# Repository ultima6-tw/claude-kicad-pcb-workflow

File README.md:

# How we design a PCB with Claude Code and KiCad

> **Status: workflow demonstration, NOT a verified design.**
> The example board in this repo has never been fabricated or powered on.
> Its layout is unfinished: signal routing for one of four cells is done, but power and ground planes are still in progress.
> Do not send these files to a fab, and do not reuse the circuit without your own review.
>
> **High-voltage warning:** the example design floats on a +300 V platform and uses ±52 V rails.
> If you build anything similar, follow proper isolation, creepage and safety practices. The DRC rules here only check clearance, not creepage.

This repo documents the whole process we used to design a PCB with an AI assistant (Claude Code), from datasheets to Gerber files.

The example is a 16-channel high-voltage arbitrary waveform generator: four FPGA modules (Trenz TE0720), each driving four AD8460 DACs, with isolated power on one 300 × 290 mm, 6-layer board.

The main idea: **the AI handles the schematic the way it handles code.** Connections are written as text, repeated structure is generated by scripts, and every step is checked by a program. Then KiCad turns the result into a board.

## The process

```
 1. Setup            KiCad 10 + KiCad MCP server + Claude Code
 2. Datasheets       every connection traced to a datasheet section
 3. Parts            built-in → vendor (with fixes) → generated from datasheet
 4. Sub-circuits     parts + net labels on pins, no wires          → ERC
 5. Hierarchy        generated by script                           → pin-by-pin check
 6. Into the board   kicad-cli netlist written into pads           → schematic parity
 7. Design rules     net classes + high-voltage clearance          → negative test
 8. Placement        script (or KiCad GUI)
 9. Routing          script (or KiCad GUI)                         → DRC
10. Output           Gerber, drill, BOM, position files
```

### 1. Setup
KiCad 10.0.6, [mixelpixx/KiCAD-MCP-Server](https://github.com/mixelpixx/KiCAD-MCP-Server), and Claude Code on macOS. Install steps and common problems are in [`docs/kicad-mcp-setup.md`](docs/kicad-mcp-setup.md).

We first ran a tiny LED + resistor board through the full flow (schematic → ERC → PCB → DRC → Gerber) to make sure the tool chain works before starting real work.

### 2. Read the datasheets first
Before drawing anything, Claude reads the datasheets and application notes and writes down where each connection comes from (for example, "AD8460 datasheet, Figure 58"). If a choice has no reference, it is labelled **"no reference, design decision"**, so a reviewer knows what to double-check. These notes are kept next to the design as a running log.

### 3. Parts
In this order:
1. **KiCad built-in libraries** where possible.
2. **Vendor libraries** (Ultra Librarian), imported by a script that also fixes their errors. We found wrong pin types, an exposed pad with no matching symbol pin, and one part with the wrong package.
3. **Generated from the datasheet** when nothing exists. For example, `gen_te0720.py` reads connector pins from the module's schematic PDF. Every dimension is then compared with the official drawing.

### 4. Sub-circuits
Each sub-circuit (one DAC channel, the power stage) is drawn through the MCP server. Parts are placed, and **net labels are put directly on pins instead of drawing wires**. The schematic is then effectively a text netlist that is easy to read, diff and check. ERC runs after each sub-circuit.

### 5. Hierarchy
`build_integrated.py` assembles the full design: root → POWER, CELL ×4 → DAC ×4 (693 parts, 22 sheets). One DAC sheet is reused 16 times, with reference designators offset per instance. `check_integrated.py` then compares every pin against each sub-circuit's netlist, for example all 256 FPGA↔DAC signals.

### 6. Into the board
The MCP command `sync_schematic_to_board` creates the footprints. It could not assign nets in a reused multi-level hierarchy, so `assign_nets.py` writes the `kicad-cli` netlist into the pads. `kicad-cli pcb drc --schematic-parity` confirms that the board matches the schematic (0 issues).

### 7. Design rules
`apply_netclass.py` assigns nets to the isolated side A and the high-voltage side B. A custom rule requires ≥ 2.5 mm between them. `test_hv_rule.py` then places a deliberate violation and checks that DRC catches it. **A rule that has never failed has not been tested.**

### 8–9. Placement and routing
We scripted these to see how far it goes. `place_board.py` places one cell. `route_cell.py` is a grid A* router that routed all 136 signal nets of one cell after three rounds (about 17 minutes). It only finds a path: it does not optimize length or impedance. For most boards, placing and routing in the KiCad GUI is probably the more practical choice.

### 10. Output
Gerber, drill, BOM and position files are exported with `kicad-cli`. This was done for the LED test board and a smaller isolated power board, but not yet for the example board.

## Pitfalls we hit

Each of these failed **silently**: no error, and the checks still looked clean.

- **Net classes vanish → high-voltage rules stop working, DRC still passes.** `pcbnew.LoadBoard` from a folder without a `.kicad_pro`, then `SaveBoard` into a folder that has one, overwrites the project file with defaults.
- **MCP `create_netclass`** reported success but did not write the net assignments to `.kicad_pro`.
- **Hierarchical net names:** the board may say `VIN_FILT` while the schematic says `/VIN_FILT`. Net-class patterns must cover both forms.
- **Zone fill uses whatever project file is next to the board.** Fill with the wrong `.kicad_pro` and the copper ignores your clearance rules.
- **MCP keeps the board in memory.** After a script edits the file, call `reload_board` / `open_project` before using MCP again.
- **After upgrading KiCad, restart the Claude Code session**, or the MCP server keeps using the old `pcbnew`.
- **KiCad DRC caps each violation type at about 200 entries.** Check a copy of the board with only the parts you are working on, or real problems get buried.

## Third-party material

We respect the terms of every source we used. Some files are therefore **not in this repo**, and you need to get them yourself.

**You can open the design without them.** KiCad stores a copy of each symbol and footprint inside the `.kicad_sch` and `.kicad_pcb` files. You only need the items below if you want to re-run the part scripts.

On a fresh clone, ERC reports 10 warnings, `lib_symbol_issues` and `footprint_link_issues`, for the five missing Ultra Librarian libraries. This is expected. There are no other ERC violations.

### Ultra Librarian parts (not included)

Some parts come from [Ultra Librarian](https://www.ultralibrarian.com/). Their agreement allows designs that use these parts to be shared, including as open source, but it does not allow redistributing the part libraries themselves. Download these parts yourself in KiCad format:

| Part | Used for |
|---|---|
| AD8460BSVZ | High-voltage DAC (16×) |
| REF5050IDR | 5 V reference |
| TPS75233QPWPR | 3.3 V LDO |
| REC15E-2405SZ | Isolated 5 V supply |
| R3M-2409S (SMD) | Isolated 9 V supply |

Then run the import scripts. They copy the parts into the project and apply our fixes, which are written in the scripts so you can see what was changed and why:

```bash
python3 tools/import_ul_ad8460.py <your-library>/KICAD/v9 kicad/lib
python3 tools/import_ul_parts.py  <your-library>/KICAD/v9 kicad/lib
```

The symbols and footprints of these parts that are embedded in the design files remain the property of EMA Design Automation (Ultra Librarian) or the manufacturer. They are **not** covered by this repo's license.

### Trenz TE0720 pin table (not included)

`tools/gen_te0720.py` builds the module's connector symbol from a pin table. That table is extracted from the TE0720 schematic, which Trenz Electronic does not allow to be reproduced. To rebuild it, download the TE0720 schematic (Rev 04) from the [Trenz Electronic wiki](https://wiki.trenz-electronic.de/display/PD/TE0720+TRM), then:

```bash
pdftotext -f 5 -l 5 -bbox TE0720-04_schematic.pdf page5.html   # pdftotext is part of poppler
python3 tools/extract_te0720_pins.py page5.html kicad/lib/te0720_pins.json
```

### KiCad libraries

The TE0720 footprint reuses the pad geometry of KiCad's built-in Samtec LSHM footprints. For this reason, `kicad/lib/` is licensed under CC-BY-SA 4.0, the same license as the [KiCad libraries](https://www.kicad.org/libraries/license/). The other parts we made ourselves from datasheets (CQB150W, LMK1C1106A) are in the same folder and use the same license.

### Datasheets

We only link to datasheets and do not include them. Symbols and footprints follow the manufacturers' published data.

## What "verified" means here

The program checks prove that **the wiring matches the design intent**. They do not prove that the design is correct. There was no simulation, no fabrication and no measurement.

## Repository layout

```
docs/kicad-mcp-setup.md    install and troubleshooting guide for the KiCad MCP server
kicad/hv_awg/              the full board: schematic hierarchy, PCB, design rules
kicad/ad8460/              one DAC channel (sub-circuit source)
kicad/power/               power stage (sub-circuit source)
kicad/lib/                 parts we made: TE0720, CQB150W, LMK1C1106A
tools/                     part generators, hierarchy builder, checks, placement and routing
```

## Versions

KiCad 10.0.6 · mixelpixx/KiCAD-MCP-Server (main) · Claude Code · macOS (Apple Silicon)

## License

| Part of the repo | License |
|---|---|
| `tools/`, `docs/`, README, design files in `kicad/hv_awg/`, `kicad/ad8460/`, `kicad/power/` | MIT |
| `kicad/lib/` | CC-BY-SA 4.0 (contains data derived from the KiCad libraries) |
| Ultra Librarian symbols and footprints embedded in the design files | Not ours. © EMA Design Automation or the manufacturer |

This repo was produced with Claude Code (Anthropic).

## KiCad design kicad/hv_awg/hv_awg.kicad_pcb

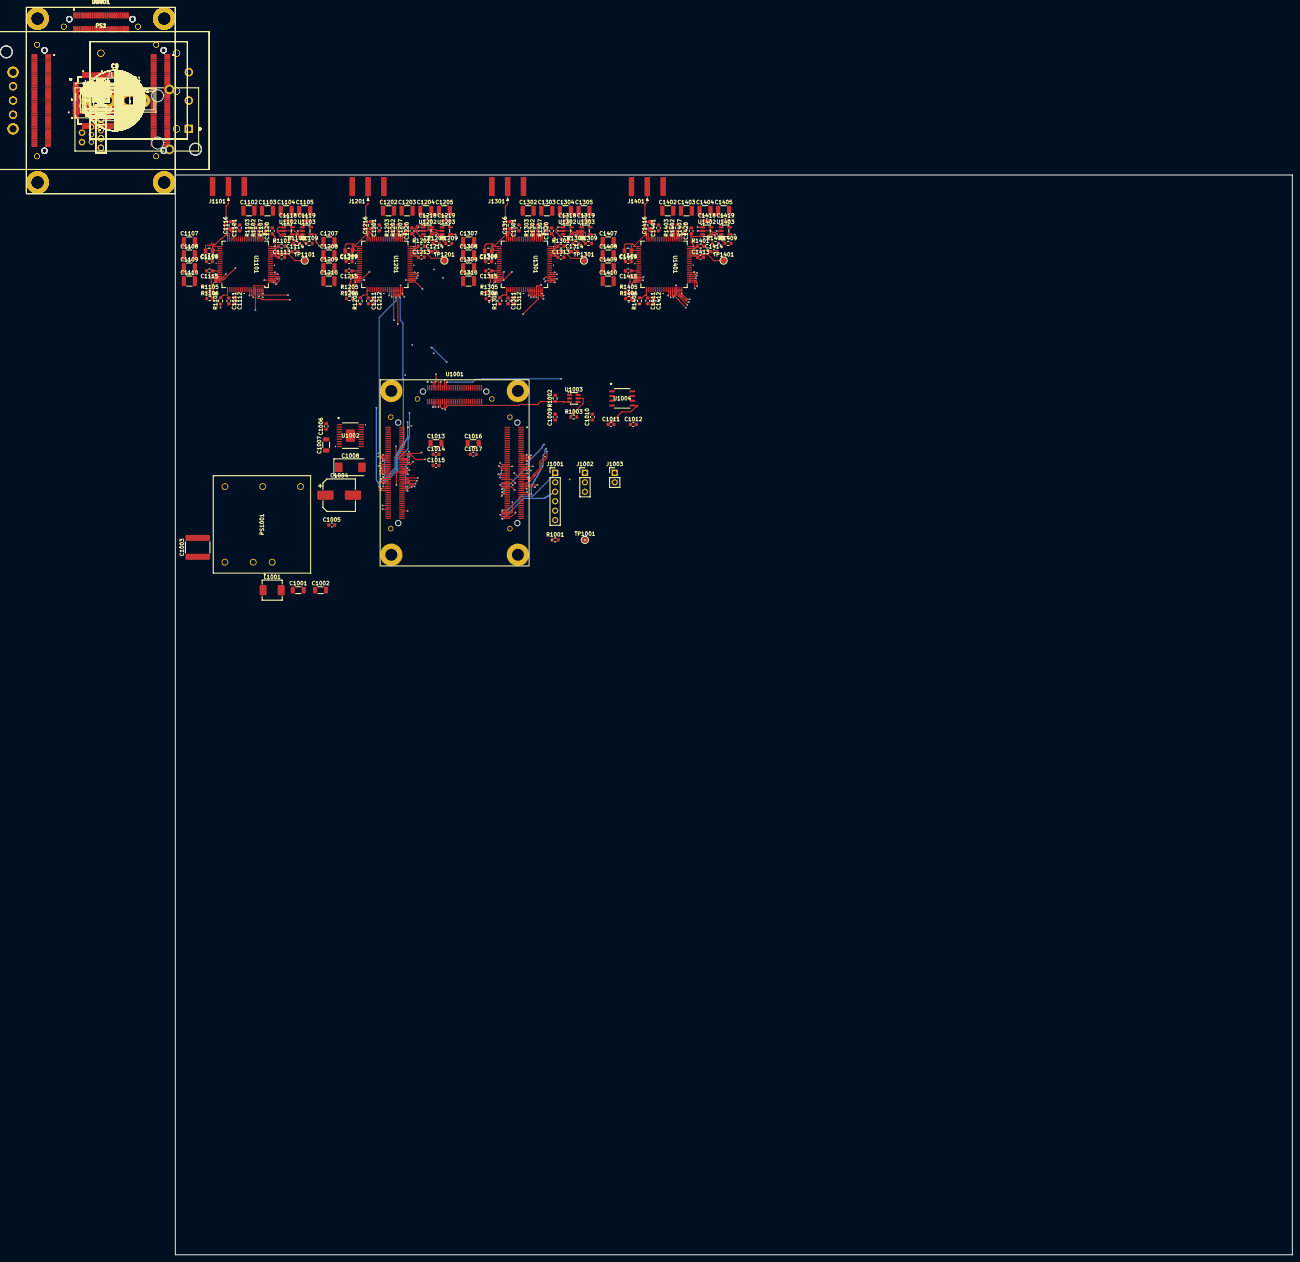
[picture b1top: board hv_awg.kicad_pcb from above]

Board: 6 copper layers, 300.0 x 290.0 mm, 723 parts (0 on the bottom side), 618 nets.

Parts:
C1, C2, C3, C8, C9: 220uF 100V; CP_Radial_D16.0mm_P7.50mm
C4, C6: 1uF 100V; C_1210_3225Metric
C5, C7: 10uF 100V; CP_Elec_8x10
C10: 10uF 25V; C_1206_3216Metric
C11, C104, C105, C106, C107, C108, C109, C110, C111, C112, C1005, C1009, C1010, C1014, C1015, C1017, C1111, C1112, C1113, C1114, C1115, C1118, C1119, C1211, C1212, C1213, C1214, C1215, C1218, C1219, C1311, C1312, C1313, C1314, C1315, C1318, C1319, C1411, C1412, C1413, C1414, C1415, C1418, C1419, C2005, C2009, C2010, C2014, C2015, C2017, C2111, C2112, C2113, C2114, C2115, C2118, C2119, C2211, C2212, C2213, C2214, C2215, C2218, C2219, C2311, C2312, C2313, C2314, C2315, C2318, C2319, C2411, C2412, C2413, C2414, C2415, C2418, C2419, C3005, C3009, C3010, C3014, C3015, C3017, C3111, C3112, C3113, C3114, C3115, C3118, C3119, C3211, C3212, C3213, C3214, C3215, C3218, C3219, C3311, C3312, C3313, C3314, C3315, C3318, C3319, C3411, C3412, C3413, C3414, C3415, C3418, C3419, C4005, C4009, C4010, C4014, C4015, C4017, C4111, C4112, C4113, C4114, C4115, C4118, C4119, C4211, C4212, C4213, C4214, C4215, C4218, C4219, C4311, C4312, C4313, C4314, C4315, C4318, C4319, C4411, C4412, C4413, C4414, C4415, C4418, C4419: 0.1uF; C_0603_1608Metric
C101: 100nF 50V; C_0603_1608Metric
C102: 100pF 1kV; C_1206_3216Metric
C103, C1007, C1013, C1016, C2007, C2013, C2016, C3007, C3013, C3016, C4007, C4013, C4016: 10uF; C_1206_3216Metric
C1001, C1002, C2001, C2002, C3001, C3002, C4001, C4002: 2.2uF 100V; C_1206_3216Metric
C1003, C2003, C3003, C4003: 1.5nF 2kV; C_2225_5664Metric
C1004, C2004, C3004, C4004: 47uF 16V; CP_Elec_8x10.5
C1006, C1011, C1012, C2006, C2011, C2012, C3006, C3011, C3012, C4006, C4011, C4012: 1uF; C_0603_1608Metric
C1008, C2008, C3008, C4008: 100uF 10V Ta ESR>100m; CP_EIA-7343-31_Kemet-D
C1101, C1106, C1201, C1206, C1301, C1306, C1401, C1406, C2101, C2106, C2201, C2206, C2301, C2306, C2401, C2406, C3101, C3106, C3201, C3206, C3301, C3306, C3401, C3406, C4101, C4106, C4201, C4206, C4301, C4306, C4401, C4406: 0.1uF 100V; C_0603_1608Metric
C1102, C1103, C1104, C1105, C1107, C1108, C1109, C1110, C1202, C1203, C1204, C1205, C1207, C1208, C1209, C1210, C1302, C1303, C1304, C1305, C1307, C1308, C1309, C1310, C1402, C1403, C1404, C1405, C1407, C1408, C1409, C1410, C2102, C2103, C2104, C2105, C2107, C2108, C2109, C2110, C2202, C2203, C2204, C2205, C2207, C2208, C2209, C2210, C2302, C2303, C2304, C2305, C2307, C2308, C2309, C2310, C2402, C2403, C2404, C2405, C2407, C2408, C2409, C2410, C3102, C3103, C3104, C3105, C3107, C3108, C3109, C3110, C3202, C3203, C3204, C3205, C3207, C3208, C3209, C3210, C3302, C3303, C3304, C3305, C3307, C3308, C3309, C3310, C3402, C3403, C3404, C3405, C3407, C3408, C3409, C3410, C4102, C4103, C4104, C4105, C4107, C4108, C4109, C4110, C4202, C4203, C4204, C4205, C4207, C4208, C4209, C4210, C4302, C4303, C4304, C4305, C4307, C4308, C4309, C4310, C4402, C4403, C4404, C4405, C4407, C4408, C4409, C4410: 1.2uF 100V; C_1210_3225Metric
C1116, C1117, C1216, C1217, C1316, C1317, C1416, C1417, C2116, C2117, C2216, C2217, C2316, C2317, C2416, C2417, C3116, C3117, C3216, C3217, C3316, C3317, C3416, C3417, C4116, C4117, C4216, C4217, C4316, C4317, C4416, C4417: 10pF 200V C0G; C_0805_2012Metric
C1120, C1220, C1320, C1420, C2120, C2220, C2320, C2420, C3120, C3220, C3320, C3420, C4120, C4220, C4320, C4420: 100pF DNP; C_0603_1608Metric
D1: SMDJ40CA; D_SMC
D2, D3: SS510; D_SMC
F1: 20A T; Fuse_Blade_ATO_directSolder
J1: 24V IN; TerminalBlock_Phoenix_MKDS-3-2-5.08_1x02_P5.08mm_Horizontal
J101: JK0654219NL; RJ45_Pulse_JK0654219NL_Horizontal
J102: CLK_IN; SMA_Amphenol_132289_EdgeMount
J103: CLK_OUT; SMA_Amphenol_132289_EdgeMount
J104: TRIG_IN; SMA_Amphenol_132289_EdgeMount
J105: TRIG_OUT; SMA_Amphenol_132289_EdgeMount
J1001, J2001, J3001, J4001: JTAG; PinHeader_1x06_P2.54mm_Vertical
J1002, J2002, J3002, J4002: UART; PinHeader_1x03_P2.54mm_Vertical
J1003, J2003, J3003, J4003: MODE: open=QSPI, short=SD; PinHeader_1x02_P2.54mm_Vertical
J1101, J1201, J1301, J1401, J2101, J2201, J2301, J2401, J3101, J3201, J3301, J3401, J4101, J4201, J4301, J4401: SMA OUT; SMA_Amphenol_132289_EdgeMount
L1, L2, L3, L4: 1uH; L_Coilcraft_XAL7030-102
L1001, L2001, L3001, L4001: 4.7uH IHLP2020; L_Vishay_IHLP-2020
PS1, PS2: CQB150W-24S48; CQB150W
PS3: R3M-2409S; R3M_SMD_RCP
PS1001, PS2001, PS3001, PS4001: REC15E-2405SZ; REC15E-2415SZ_RCP
R1, R2: 13.3k; R_0603_1608Metric
R101, R104, R1104, R1204, R1304, R1404, R2104, R2204, R2304, R2404, R3104, R3204, R3304, R3404, R4104, R4204, R4304, R4404: 33R; R_0603_1608Metric
R102, R103, R105, R106, R107, R108, R109, R110, R111, R1001, R1002, R1105, R1106, R1107, R1205, R1206, R1207, R1305, R1306, R1307, R1405, R1406, R1407, R2001, R2002, R2105, R2106, R2107, R2205, R2206, R2207, R2305, R2306, R2307, R2405, R2406, R2407, R3001, R3002, R3105, R3106, R3107, R3205, R3206, R3207, R3305, R3306, R3307, R3405, R3406, R3407, R4001, R4002, R4105, R4106, R4107, R4205, R4206, R4207, R4305, R4306, R4307, R4405, R4406, R4407: 10k; R_0603_1608Metric
R112: 1M 1kV; R_2512_6332Metric
R1003, R2003, R3003, R4003: 100R; R_0603_1608Metric
R1101, R1201, R1301, R1401, R2101, R2201, R2301, R2401, R3101, R3201, R3301, R3401, R4101, R4201, R4301, R4401: 2k 0.1%; R_0603_1608Metric
R1102, R1103, R1202, R1203, R1302, R1303, R1402, R1403, R2102, R2103, R2202, R2203, R2302, R2303, R2402, R2403, R3102, R3103, R3202, R3203, R3302, R3303, R3402, R3403, R4102, R4103, R4202, R4203, R4302, R4303, R4402, R4403: 50R 0.1%; R_0603_1608Metric
R1108, R1109, R1208, R1209, R1308, R1309, R1408, R1409, R2108, R2109, R2208, R2209, R2308, R2309, R2408, R2409, R3108, R3109, R3208, R3209, R3308, R3309, R3408, R3409, R4108, R4109, R4208, R4209, R4308, R4309, R4408, R4409: 49.9k; R_0603_1608Metric
TP1001, TP2001, TP3001, TP4001: PGOOD; TestPoint_Pad_D1.5mm
TP1101, TP1201, TP1301, TP1401, TP2101, TP2201, TP2301, TP2401, TP3101, TP3201, TP3301, TP3401, TP4101, TP4201, TP4301, TP4401: TMP; TestPoint_Pad_D1.5mm
U101, U103: SN74LVC2G157DCU; VSSOP-8_2.3x2mm_P0.5mm
U102, U104: LMK1C1106APWR; TSSOP-14_4.4x5mm_P0.65mm
U1001, U2001, U3001, U4001: TE0720-04; TE0720
U1002, U2002, U3002, U4002: TPS75233QPWPR; PWP20
U1003, U2003, U3003, U4003: TPS22810DBV; SOT-23-6
U1004, U2004, U3004, U4004: REF5050IDR; D8
U1101, U1201, U1301, U1401, U2101, U2201, U2301, U2401, U3101, U3201, U3301, U3401, U4101, U4201, U4301, U4401: AD8460BSVZ; SV-80-7_ADI
U1102, U1202, U1302, U1402, U2102, U2202, U2302, U2402, U3102, U3202, U3302, U3402, U4102, U4202, U4302, U4402: SN74LVC1G125DBV; SOT-23-5
U1103, U1203, U1303, U1403, U2103, U2203, U2303, U2403, U3103, U3203, U3303, U3403, U4103, U4203, U4303, U4403: SN74LVC1G17DBV; SOT-23-5
Y101: 50MHz 3.3V; Oscillator_SMD_Abracon_ASE-4Pin_3.2x2.5mm

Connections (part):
/CELL1/BOOT_MODE: J1003.1, U1001.JB1.31
/CELL1/D1_CS_N: R1105.2, U1001.JB1.50, U1101.40
/CELL1/D1_DB0: U1001.JB1.32, U1101.53
/CELL1/D1_DB1: U1001.JB1.34, U1101.54
/CELL1/D1_DB2: U1001.JB1.35, U1101.55
/CELL1/D1_DB3: U1001.JB1.36, U1101.56
/CELL1/D1_DB4: U1001.JB1.37, U1101.57
/CELL1/D1_DB5: U1001.JB1.38, U1101.58
/CELL1/D1_DB6: U1001.JB1.39, U1101.59
/CELL1/D1_DB7: U1001.JB1.41, U1101.60
/CELL1/D1_DB8: U1001.JB1.42, U1101.61
/CELL1/D1_DB9: U1001.JB1.44, U1101.62
/CELL1/D1_DB10: U1001.JB1.45, U1101.63
/CELL1/D1_DB11: U1001.JB1.46, U1101.64
/CELL1/D1_DB12: U1001.JB1.47, U1101.65
/CELL1/D1_DB13: U1001.JB1.48, U1101.66
/CELL1/D1_SYNC: R1104.1, U1001.JB1.49
/CELL1/D2_CS_N: R1205.2, U1001.JB1.70, U1201.40
/CELL1/D2_DB0: U1001.JB1.51, U1201.53
/CELL1/D2_DB1: U1001.JB1.52, U1201.54
/CELL1/D2_DB2: U1001.JB1.55, U1201.55
/CELL1/D2_DB3: U1001.JB1.56, U1201.56
/CELL1/D2_DB4: U1001.JB1.57, U1201.57
/CELL1/D2_DB5: U1001.JB1.58, U1201.58
/CELL1/D2_DB6: U1001.JB1.59, U1201.59
/CELL1/D2_DB7: U1001.JB1.60, U1201.60
/CELL1/D2_DB8: U1001.JB1.61, U1201.61
/CELL1/D2_DB9: U1001.JB1.62, U1201.62
/CELL1/D2_DB10: U1001.JB1.65, U1201.63
/CELL1/D2_DB11: U1001.JB1.66, U1201.64
/CELL1/D2_DB12: U1001.JB1.67, U1201.65
/CELL1/D2_DB13: U1001.JB1.68, U1201.66
/CELL1/D2_SYNC: R1204.1, U1001.JB1.69
/CELL1/D3_CS_N: R1305.2, U1001.JB2.54, U1301.40
/CELL1/D3_DB0: U1001.JB2.31, U1301.53
/CELL1/D3_DB1: U1001.JB2.33, U1301.54
/CELL1/D3_DB2: U1001.JB2.35, U1301.55
/CELL1/D3_DB3: U1001.JB2.37, U1301.56
/CELL1/D3_DB4: U1001.JB2.41, U1301.57
/CELL1/D3_DB5: U1001.JB2.42, U1301.58
/CELL1/D3_DB6: U1001.JB2.43, U1301.59
/CELL1/D3_DB7: U1001.JB2.44, U1301.60
/CELL1/D3_DB8: U1001.JB2.45, U1301.61
/CELL1/D3_DB9: U1001.JB2.46, U1301.62
/CELL1/D3_DB10: U1001.JB2.47, U1301.63
/CELL1/D3_DB11: U1001.JB2.48, U1301.64
/CELL1/D3_DB12: U1001.JB2.51, U1301.65
/CELL1/D3_DB13: U1001.JB2.52, U1301.66
/CELL1/D3_SYNC: R1304.1, U1001.JB2.53
/CELL1/D4_CS_N: R1405.2, U1001.JB2.74, U1401.40
/CELL1/D4_DB0: U1001.JB2.55, U1401.53
/CELL1/D4_DB1: U1001.JB2.56, U1401.54
/CELL1/D4_DB2: U1001.JB2.57, U1401.55
/CELL1/D4_DB3: U1001.JB2.58, U1401.56
/CELL1/D4_DB4: U1001.JB2.61, U1401.57
/CELL1/D4_DB5: U1001.JB2.62, U1401.58
/CELL1/D4_DB6: U1001.JB2.63, U1401.59
/CELL1/D4_DB7: U1001.JB2.64, U1401.60
/CELL1/D4_DB8: U1001.JB2.65, U1401.61
/CELL1/D4_DB9: U1001.JB2.66, U1401.62
/CELL1/D4_DB10: U1001.JB2.67, U1401.63
/CELL1/D4_DB11: U1001.JB2.68, U1401.64
/CELL1/D4_DB12: U1001.JB2.71, U1401.65
/CELL1/D4_DB13: U1001.JB2.72, U1401.66
/CELL1/D4_SYNC: R1404.1, U1001.JB2.73
/CELL1/DAC1/AVDD_3P3V: C1113.1, U1101.75, U1101.76
/CELL1/DAC1/COMP_H: C1116.1, U1101.17
/CELL1/DAC1/COMP_L: C1117.1, U1101.23
/CELL1/DAC1/COMP_T: C1115.1, U1101.34
/CELL1/DAC1/FS_ADJ: R1101.1, U1101.79
/CELL1/DAC1/IOUTN: R1103.1, U1101.5, U1101.6
/CELL1/DAC1/IOUTP: R1102.1, U1101.3, U1101.4
/CELL1/DAC1/OUT: C1116.2, C1117.2, J1101.1, U1101.19, U1101.20, U1101.21
/CELL1/DAC1/REFIO: C1114.1, U1101.78
/CELL1/DAC1/SDN_IO: C1120.1, U1101.80, U1102.4, U1103.2
/CELL1/DAC1/SYNC_D: R1104.2, U1101.41
/CELL1/DAC1/TMP: TP1101.1, U1101.77
/CELL1/DAC2/AVDD_3P3V: C1213.1, U1201.75, U1201.76
/CELL1/DAC2/COMP_H: C1216.1, U1201.17
/CELL1/DAC2/COMP_L: C1217.1, U1201.23
/CELL1/DAC2/COMP_T: C1215.1, U1201.34
/CELL1/DAC2/FS_ADJ: R1201.1, U1201.79
/CELL1/DAC2/IOUTN: R1203.1, U1201.5, U1201.6
/CELL1/DAC2/IOUTP: R1202.1, U1201.3, U1201.4
/CELL1/DAC2/OUT: C1216.2, C1217.2, J1201.1, U1201.19, U1201.20, U1201.21
/CELL1/DAC2/REFIO: C1214.1, U1201.78
/CELL1/DAC2/SDN_IO: C1220.1, U1201.80, U1202.4, U1203.2
/CELL1/DAC2/SYNC_D: R1204.2, U1201.41
/CELL1/DAC2/TMP: TP1201.1, U1201.77
/CELL1/DAC3/AVDD_3P3V: C1313.1, U1301.75, U1301.76
/CELL1/DAC3/COMP_H: C1316.1, U1301.17
/CELL1/DAC3/COMP_L: C1317.1, U1301.23
/CELL1/DAC3/COMP_T: C1315.1, U1301.34
/CELL1/DAC3/FS_ADJ: R1301.1, U1301.79
/CELL1/DAC3/IOUTN: R1303.1, U1301.5, U1301.6
/CELL1/DAC3/IOUTP: R1302.1, U1301.3, U1301.4
/CELL1/DAC3/OUT: C1316.2, C1317.2, J1301.1, U1301.19, U1301.20, U1301.21
/CELL1/DAC3/REFIO: C1314.1, U1301.78
/CELL1/DAC3/SDN_IO: C1320.1, U1301.80, U1302.4, U1303.2
/CELL1/DAC3/SYNC_D: R1304.2, U1301.41
/CELL1/DAC3/TMP: TP1301.1, U1301.77
/CELL1/DAC4/AVDD_3P3V: C1413.1, U1401.75, U1401.76
/CELL1/DAC4/COMP_H: C1416.1, U1401.17
/CELL1/DAC4/COMP_L: C1417.1, U1401.23
/CELL1/DAC4/COMP_T: C1415.1, U1401.34
/CELL1/DAC4/FS_ADJ: R1401.1, U1401.79
/CELL1/DAC4/IOUTN: R1403.1, U1401.5, U1401.6
/CELL1/DAC4/IOUTP: R1402.1, U1401.3, U1401.4
/CELL1/DAC4/OUT: C1416.2, C1417.2, J1401.1, U1401.19, U1401.20, U1401.21
/CELL1/DAC4/REFIO: C1414.1, U1401.78
/CELL1/DAC4/SDN_IO: C1420.1, U1401.80, U1402.4, U1403.2
/CELL1/DAC4/SYNC_D: R1404.2, U1401.41
/CELL1/DAC4/TMP: TP1401.1, U1401.77
/CELL1/JTAGMODE: R1001.1, U1001.JB1.90
/CELL1/P3V3_IN: C1008.1, C1015.1, U1001.JB1.14, U1001.JB1.16, U1002.7, U1002.8, U1002.9
/CELL1/P5V: C1004.1, C1005.1, C1006.1, C1007.1, C1013.1, C1014.1, C1111.1, C1211.1, C1311.1, C1411.1, PS1001.6, U1001.JB1.2, U1001.JB1.4, U1001.JB1.6, U1001.JB2.1, U1001.JB2.3, U1001.JB2.5, U1001.JB2.7, U1002.3, U1002.4, U1101.42, U1201.42, U1301.42, U1401.42
/CELL1/PGOOD: TP1001.1, U1001.JB1.29
/CELL1/RESET_N: R1106.2, R1206.2, R1306.2, R1406.2, U1001.JB3.10, U1101.36, U1201.36, U1301.36, U1401.36
/CELL1/SCLK: U1001.JB3.7, U1101.39, U1201.39, U1301.39, U1401.39
/CELL1/SDI: U1001.JB3.8, U1101.38, U1201.38, U1301.38, U1401.38
/CELL1/SDN_DRV: R1109.1, R1209.1, R1309.1, R1409.1, U1001.JB3.14, U1102.2, U1202.2, U1302.2, U1402.2
/CELL1/SDN_FLAG1: U1001.JB3.16, U1103.4
/CELL1/SDN_FLAG2: U1001.JB3.19, U1203.4
/CELL1/SDN_FLAG3: U1001.JB3.20, U1303.4
/CELL1/SDN_FLAG4: U1001.JB3.21, U1403.4
/CELL1/SDN_OE_N: R1108.2, R1208.2, R1308.2, R1408.2, U1001.JB3.15, U1102.1, U1202.1, U1302.1, U1402.1
/CELL1/SDN_RESET: R1107.1, R1207.1, R1307.1, R1407.1, U1001.JB3.13, U1101.1, U1201.1, U1301.1, U1401.1
/CELL1/SDO: U1001.JB3.9, U1101.37, U1201.37, U1301.37, U1401.37
/CELL1/UART_MIO14: J1002.1, U1001.JB1.91
/CELL1/UART_MIO15: J1002.2, U1001.JB1.86
/CELL1/VIN_5: L1001.1, PS1001.1
/CELL1/VREF_5V: C1012.1, C1112.1, C1212.1, C1312.1, C1412.1, U1004.6, U1101.44, U1201.44, U1301.44, U1401.44
/CELL1/VREF_EN: R1002.1, U1001.JB3.22, U1003.3
/CELL1/VREF_IN: C1010.1, R1003.2, U1003.6, U1004.2
/CELL1/VREF_JTAG: J1001.1, U1001.JB2.92
/CELL1/VREF_NR: C1011.1, U1004.5
/CELL1/VREF_QOD: R1003.1, U1003.5
/CELL1/X_TCK: J1001.3, U1001.JB2.100
/CELL1/X_TDI: J1001.5, U1001.JB2.96
/CELL1/X_TDO: J1001.4, U1001.JB2.98
/CELL1/X_TMS: J1001.2, U1001.JB2.94
/CELL1_P3V3: C103.1, C104.1, C105.1, C106.1, C107.1, C108.1, C109.1, C110.1, C111.1, C112.1, C1016.1, C1017.1, C1118.1, C1119.1, C1218.1, C1219.1, C1318.1, C1319.1, C1418.1, C1419.1, R109.1, R110.1, R111.1, R1105.1, R1106.1, R1108.1, R1205.1, R1206.1, R1208.1, R1305.1, R1306.1, R1308.1, R1405.1, R1406.1, R1408.1, U101.8, U102.5, U102.8, U102.12, U103.8, U104.5, U104.8, U104.12, U1001.JB1.10, U1001.JB1.12, U1001.JB2.2, U1001.JB2.4, U1001.JB2.6, U1001.JB2.8, U1001.JB2.9, U1001.JB2.10, U1001.JB2.11, U1102.5, U1103.5, U1202.5, U1203.5, U1302.5, U1303.5, U1402.5, U1403.5, Y101.1, Y101.4
/CELL2/BOOT_MODE: J2003.1, U2001.JB1.31
/CELL2/D1_CS_N: R2105.2, U2001.JB1.50, U2101.40
/CELL2/D1_DB0: U2001.JB1.32, U2101.53
/CELL2/D1_DB1: U2001.JB1.34, U2101.54
/CELL2/D1_DB2: U2001.JB1.35, U2101.55
/CELL2/D1_DB3: U2001.JB1.36, U2101.56
/CELL2/D1_DB4: U2001.JB1.37, U2101.57
/CELL2/D1_DB5: U2001.JB1.38, U2101.58
/CELL2/D1_DB6: U2001.JB1.39, U2101.59
/CELL2/D1_DB7: U2001.JB1.41, U2101.60
/CELL2/D1_DB8: U2001.JB1.42, U2101.61
/CELL2/D1_DB9: U2001.JB1.44, U2101.62
/CELL2/D1_DB10: U2001.JB1.45, U2101.63
/CELL2/D1_DB11: U2001.JB1.46, U2101.64
/CELL2/D1_DB12: U2001.JB1.47, U2101.65
/CELL2/D1_DB13: U2001.JB1.48, U2101.66
/CELL2/D1_SYNC: R2104.1, U2001.JB1.49
/CELL2/D2_CS_N: R2205.2, U2001.JB1.70, U2201.40
/CELL2/D2_DB0: U2001.JB1.51, U2201.53
/CELL2/D2_DB1: U2001.JB1.52, U2201.54
/CELL2/D2_DB2: U2001.JB1.55, U2201.55
/CELL2/D2_DB3: U2001.JB1.56, U2201.56
/CELL2/D2_DB4: U2001.JB1.57, U2201.57
/CELL2/D2_DB5: U2001.JB1.58, U2201.58
/CELL2/D2_DB6: U2001.JB1.59, U2201.59
/CELL2/D2_DB7: U2001.JB1.60, U2201.60
/CELL2/D2_DB8: U2001.JB1.61, U2201.61
/CELL2/D2_DB9: U2001.JB1.62, U2201.62
/CELL2/D2_DB10: U2001.JB1.65, U2201.63
/CELL2/D2_DB11: U2001.JB1.66, U2201.64
/CELL2/D2_DB12: U2001.JB1.67, U2201.65
/CELL2/D2_DB13: U2001.JB1.68, U2201.66
/CELL2/D2_SYNC: R2204.1, U2001.JB1.69
/CELL2/D3_CS_N: R2305.2, U2001.JB2.54, U2301.40
/CELL2/D3_DB0: U2001.JB2.31, U2301.53
/CELL2/D3_DB1: U2001.JB2.33, U2301.54
/CELL2/D3_DB2: U2001.JB2.35, U2301.55
/CELL2/D3_DB3: U2001.JB2.37, U2301.56
/CELL2/D3_DB4: U2001.JB2.41, U2301.57
/CELL2/D3_DB5: U2001.JB2.42, U2301.58
/CELL2/D3_DB6: U2001.JB2.43, U2301.59
/CELL2/D3_DB7: U2001.JB2.44, U2301.60
/CELL2/D3_DB8: U2001.JB2.45, U2301.61
/CELL2/D3_DB9: U2001.JB2.46, U2301.62
/CELL2/D3_DB10: U2001.JB2.47, U2301.63
/CELL2/D3_DB11: U2001.JB2.48, U2301.64
/CELL2/D3_DB12: U2001.JB2.51, U2301.65
/CELL2/D3_DB13: U2001.JB2.52, U2301.66
/CELL2/D3_SYNC: R2304.1, U2001.JB2.53
/CELL2/D4_CS_N: R2405.2, U2001.JB2.74, U2401.40
/CELL2/D4_DB0: U2001.JB2.55, U2401.53
/CELL2/D4_DB1: U2001.JB2.56, U2401.54
/CELL2/D4_DB2: U2001.JB2.57, U2401.55
/CELL2/D4_DB3: U2001.JB2.58, U2401.56
/CELL2/D4_DB4: U2001.JB2.61, U2401.57
/CELL2/D4_DB5: U2001.JB2.62, U2401.58
/CELL2/D4_DB6: U2001.JB2.63, U2401.59
/CELL2/D4_DB7: U2001.JB2.64, U2401.60
/CELL2/D4_DB8: U2001.JB2.65, U2401.61
/CELL2/D4_DB9: U2001.JB2.66, U2401.62
/CELL2/D4_DB10: U2001.JB2.67, U2401.63
/CELL2/D4_DB11: U2001.JB2.68, U2401.64
/CELL2/D4_DB12: U2001.JB2.71, U2401.65
/CELL2/D4_DB13: U2001.JB2.72, U2401.66
/CELL2/D4_SYNC: R2404.1, U2001.JB2.73
/CELL2/DAC1/AVDD_3P3V: C2113.1, U2101.75, U2101.76
/CELL2/DAC1/COMP_H: C2116.1, U2101.17
/CELL2/DAC1/COMP_L: C2117.1, U2101.23
/CELL2/DAC1/COMP_T: C2115.1, U2101.34
/CELL2/DAC1/FS_ADJ: R2101.1, U2101.79
/CELL2/DAC1/IOUTN: R2103.1, U2101.5, U2101.6
/CELL2/DAC1/IOUTP: R2102.1, U2101.3, U2101.4
/CELL2/DAC1/OUT: C2116.2, C2117.2, J2101.1, U2101.19, U2101.20, U2101.21
/CELL2/DAC1/REFIO: C2114.1, U2101.78
/CELL2/DAC1/SDN_IO: C2120.1, U2101.80, U2102.4, U2103.2
/CELL2/DAC1/SYNC_D: R2104.2, U2101.41
/CELL2/DAC1/TMP: TP2101.1, U2101.77
/CELL2/DAC2/AVDD_3P3V: C2213.1, U2201.75, U2201.76
/CELL2/DAC2/COMP_H: C2216.1, U2201.17
/CELL2/DAC2/COMP_L: C2217.1, U2201.23
/CELL2/DAC2/COMP_T: C2215.1, U2201.34
/CELL2/DAC2/FS_ADJ: R2201.1, U2201.79
/CELL2/DAC2/IOUTN: R2203.1, U2201.5, U2201.6
/CELL2/DAC2/IOUTP: R2202.1, U2201.3, U2201.4
/CELL2/DAC2/OUT: C2216.2, C2217.2, J2201.1, U2201.19, U2201.20, U2201.21
/CELL2/DAC2/REFIO: C2214.1, U2201.78
/CELL2/DAC2/SDN_IO: C2220.1, U2201.80, U2202.4, U2203.2
/CELL2/DAC2/SYNC_D: R2204.2, U2201.41
/CELL2/DAC2/TMP: TP2201.1, U2201.77
/CELL2/DAC3/AVDD_3P3V: C2313.1, U2301.75, U2301.76
/CELL2/DAC3/COMP_H: C2316.1, U2301.17
/CELL2/DAC3/COMP_L: C2317.1, U2301.23
/CELL2/DAC3/COMP_T: C2315.1, U2301.34
/CELL2/DAC3/FS_ADJ: R2301.1, U2301.79
/CELL2/DAC3/IOUTN: R2303.1, U2301.5, U2301.6
/CELL2/DAC3/IOUTP: R2302.1, U2301.3, U2301.4
/CELL2/DAC3/OUT: C2316.2, C2317.2, J2301.1, U2301.19, U2301.20, U2301.21
/CELL2/DAC3/REFIO: C2314.1, U2301.78
/CELL2/DAC3/SDN_IO: C2320.1, U2301.80, U2302.4, U2303.2
/CELL2/DAC3/SYNC_D: R2304.2, U2301.41
/CELL2/DAC3/TMP: TP2301.1, U2301.77
/CELL2/DAC4/AVDD_3P3V: C2413.1, U2401.75, U2401.76
/CELL2/DAC4/COMP_H: C2416.1, U2401.17
/CELL2/DAC4/COMP_L: C2417.1, U2401.23
/CELL2/DAC4/COMP_T: C2415.1, U2401.34
/CELL2/DAC4/FS_ADJ: R2401.1, U2401.79
/CELL2/DAC4/IOUTN: R2403.1, U2401.5, U2401.6
/CELL2/DAC4/IOUTP: R2402.1, U2401.3, U2401.4
/CELL2/DAC4/OUT: C2416.2, C2417.2, J2401.1, U2401.19, U2401.20, U2401.21
/CELL2/DAC4/REFIO: C2414.1, U2401.78
/CELL2/DAC4/SDN_IO: C2420.1, U2401.80, U2402.4, U2403.2
/CELL2/DAC4/SYNC_D: R2404.2, U2401.41
/CELL2/DAC4/TMP: TP2401.1, U2401.77
/CELL2/JTAGMODE: R2001.1, U2001.JB1.90
/CELL2/P3V3: C2016.1, C2017.1, C2118.1, C2119.1, C2218.1, C2219.1, C2318.1, C2319.1, C2418.1, C2419.1, R2105.1, R2106.1, R2108.1, R2205.1, R2206.1, R2208.1, R2305.1, R2306.1, R2308.1, R2405.1, R2406.1, R2408.1, U2001.JB1.10, U2001.JB1.12, U2001.JB2.2, U2001.JB2.4, U2001.JB2.6, U2001.JB2.8, U2001.JB2.9, U2001.JB2.10, U2001.JB2.11, U2102.5, U2103.5, U2202.5, U2203.5, U2302.5, U2303.5, U2402.5, U2403.5
/CELL2/P3V3_IN: C2008.1, C2015.1, U2001.JB1.14, U2001.JB1.16, U2002.7, U2002.8, U2002.9
/CELL2/P5V: C2004.1, C2005.1, C2006.1, C2007.1, C2013.1, C2014.1, C2111.1, C2211.1, C2311.1, C2411.1, PS2001.6, U2001.JB1.2, U2001.JB1.4, U2001.JB1.6, U2001.JB2.1, U2001.JB2.3, U2001.JB2.5, U2001.JB2.7, U2002.3, U2002.4, U2101.42, U2201.42, U2301.42, U2401.42
/CELL2/PGOOD: TP2001.1, U2001.JB1.29
/CELL2/RESET_N: R2106.2, R2206.2, R2306.2, R2406.2, U2001.JB3.10, U2101.36, U2201.36, U2301.36, U2401.36
/CELL2/SCLK: U2001.JB3.7, U2101.39, U2201.39, U2301.39, U2401.39
/CELL2/SDI: U2001.JB3.8, U2101.38, U2201.38, U2301.38, U2401.38
/CELL2/SDN_DRV: R2109.1, R2209.1, R2309.1, R2409.1, U2001.JB3.14, U2102.2, U2202.2, U2302.2, U2402.2
/CELL2/SDN_FLAG1: U2001.JB3.16, U2103.4
/CELL2/SDN_FLAG2: U2001.JB3.19, U2203.4
/CELL2/SDN_FLAG3: U2001.JB3.20, U2303.4
/CELL2/SDN_FLAG4: U2001.JB3.21, U2403.4
/CELL2/SDN_OE_N: R2108.2, R2208.2, R2308.2, R2408.2, U2001.JB3.15, U2102.1, U2202.1, U2302.1, U2402.1
/CELL2/SDN_RESET: R2107.1, R2207.1, R2307.1, R2407.1, U2001.JB3.13, U2101.1, U2201.1, U2301.1, U2401.1
/CELL2/SDO: U2001.JB3.9, U2101.37, U2201.37, U2301.37, U2401.37
/CELL2/UART_MIO14: J2002.1, U2001.JB1.91
/CELL2/UART_MIO15: J2002.2, U2001.JB1.86
/CELL2/VIN_5: L2001.1, PS2001.1
/CELL2/VREF_5V: C2012.1, C2112.1, C2212.1, C2312.1, C2412.1, U2004.6, U2101.44, U2201.44, U2301.44, U2401.44
/CELL2/VREF_EN: R2002.1, U2001.JB3.22, U2003.3
/CELL2/VREF_IN: C2010.1, R2003.2, U2003.6, U2004.2
/CELL2/VREF_JTAG: J2001.1, U2001.JB2.92
/CELL2/VREF_NR: C2011.1, U2004.5
/CELL2/VREF_QOD: R2003.1, U2003.5
/CELL2/X_TCK: J2001.3, U2001.JB2.100
/CELL2/X_TDI: J2001.5, U2001.JB2.96
/CELL2/X_TDO: J2001.4, U2001.JB2.98
/CELL2/X_TMS: J2001.2, U2001.JB2.94
/CELL3/BOOT_MODE: J3003.1, U3001.JB1.31
/CELL3/D1_CS_N: R3105.2, U3001.JB1.50, U3101.40
/CELL3/D1_DB0: U3001.JB1.32, U3101.53
/CELL3/D1_DB1: U3001.JB1.34, U3101.54
/CELL3/D1_DB2: U3001.JB1.35, U3101.55
/CELL3/D1_DB3: U3001.JB1.36, U3101.56
/CELL3/D1_DB4: U3001.JB1.37, U3101.57
/CELL3/D1_DB5: U3001.JB1.38, U3101.58
/CELL3/D1_DB6: U3001.JB1.39, U3101.59
/CELL3/D1_DB7: U3001.JB1.41, U3101.60
/CELL3/D1_DB8: U3001.JB1.42, U3101.61
/CELL3/D1_DB9: U3001.JB1.44, U3101.62
/CELL3/D1_DB10: U3001.JB1.45, U3101.63
/CELL3/D1_DB11: U3001.JB1.46, U3101.64
/CELL3/D1_DB12: U3001.JB1.47, U3101.65
/CELL3/D1_DB13: U3001.JB1.48, U3101.66
/CELL3/D1_SYNC: R3104.1, U3001.JB1.49
/CELL3/D2_CS_N: R3205.2, U3001.JB1.70, U3201.40
/CELL3/D2_DB0: U3001.JB1.51, U3201.53
/CELL3/D2_DB1: U3001.JB1.52, U3201.54
/CELL3/D2_DB2: U3001.JB1.55, U3201.55
/CELL3/D2_DB3: U3001.JB1.56, U3201.56
/CELL3/D2_DB4: U3001.JB1.57, U3201.57
/CELL3/D2_DB5: U3001.JB1.58, U3201.58
/CELL3/D2_DB6: U3001.JB1.59, U3201.59
/CELL3/D2_DB7: U3001.JB1.60, U3201.60
/CELL3/D2_DB8: U3001.JB1.61, U3201.61
/CELL3/D2_DB9: U3001.JB1.62, U3201.62
/CELL3/D2_DB10: U3001.JB1.65, U3201.63
/CELL3/D2_DB11: U3001.JB1.66, U3201.64
/CELL3/D2_DB12: U3001.JB1.67, U3201.65
/CELL3/D2_DB13: U3001.JB1.68, U3201.66
/CELL3/D2_SYNC: R3204.1, U3001.JB1.69
/CELL3/D3_CS_N: R3305.2, U3001.JB2.54, U3301.40
/CELL3/D3_DB0: U3001.JB2.31, U3301.53
/CELL3/D3_DB1: U3001.JB2.33, U3301.54
/CELL3/D3_DB2: U3001.JB2.35, U3301.55
/CELL3/D3_DB3: U3001.JB2.37, U3301.56
/CELL3/D3_DB4: U3001.JB2.41, U3301.57
/CELL3/D3_DB5: U3001.JB2.42, U3301.58
/CELL3/D3_DB6: U3001.JB2.43, U3301.59
/CELL3/D3_DB7: U3001.JB2.44, U3301.60
/CELL3/D3_DB8: U3001.JB2.45, U3301.61
/CELL3/D3_DB9: U3001.JB2.46, U3301.62
/CELL3/D3_DB10: U3001.JB2.47, U3301.63
/CELL3/D3_DB11: U3001.JB2.48, U3301.64
/CELL3/D3_DB12: U3001.JB2.51, U3301.65
/CELL3/D3_DB13: U3001.JB2.52, U3301.66
/CELL3/D3_SYNC: R3304.1, U3001.JB2.53
/CELL3/D4_CS_N: R3405.2, U3001.JB2.74, U3401.40
/CELL3/D4_DB0: U3001.JB2.55, U3401.53
/CELL3/D4_DB1: U3001.JB2.56, U3401.54
/CELL3/D4_DB2: U3001.JB2.57, U3401.55
/CELL3/D4_DB3: U3001.JB2.58, U3401.56
/CELL3/D4_DB4: U3001.JB2.61, U3401.57
/CELL3/D4_DB5: U3001.JB2.62, U3401.58
/CELL3/D4_DB6: U3001.JB2.63, U3401.59
/CELL3/D4_DB7: U3001.JB2.64, U3401.60
/CELL3/D4_DB8: U3001.JB2.65, U3401.61
/CELL3/D4_DB9: U3001.JB2.66, U3401.62
/CELL3/D4_DB10: U3001.JB2.67, U3401.63
/CELL3/D4_DB11: U3001.JB2.68, U3401.64
/CELL3/D4_DB12: U3001.JB2.71, U3401.65
/CELL3/D4_DB13: U3001.JB2.72, U3401.66
/CELL3/D4_SYNC: R3404.1, U3001.JB2.73
/CELL3/DAC1/AVDD_3P3V: C3113.1, U3101.75, U3101.76
/CELL3/DAC1/COMP_H: C3116.1, U3101.17
/CELL3/DAC1/COMP_L: C3117.1, U3101.23
/CELL3/DAC1/COMP_T: C3115.1, U3101.34
/CELL3/DAC1/FS_ADJ: R3101.1, U3101.79
/CELL3/DAC1/IOUTN: R3103.1, U3101.5, U3101.6
/CELL3/DAC1/IOUTP: R3102.1, U3101.3, U3101.4
/CELL3/DAC1/OUT: C3116.2, C3117.2, J3101.1, U3101.19, U3101.20, U3101.21
/CELL3/DAC1/REFIO: C3114.1, U3101.78
/CELL3/DAC1/SDN_IO: C3120.1, U3101.80, U3102.4, U3103.2
/CELL3/DAC1/SYNC_D: R3104.2, U3101.41
/CELL3/DAC1/TMP: TP3101.1, U3101.77
/CELL3/DAC2/AVDD_3P3V: C3213.1, U3201.75, U3201.76
/CELL3/DAC2/COMP_H: C3216.1, U3201.17
/CELL3/DAC2/COMP_L: C3217.1, U3201.23
/CELL3/DAC2/COMP_T: C3215.1, U3201.34
/CELL3/DAC2/FS_ADJ: R3201.1, U3201.79
/CELL3/DAC2/IOUTN: R3203.1, U3201.5, U3201.6
/CELL3/DAC2/IOUTP: R3202.1, U3201.3, U3201.4
/CELL3/DAC2/OUT: C3216.2, C3217.2, J3201.1, U3201.19, U3201.20, U3201.21
/CELL3/DAC2/REFIO: C3214.1, U3201.78
/CELL3/DAC2/SDN_IO: C3220.1, U3201.80, U3202.4, U3203.2
/CELL3/DAC2/SYNC_D: R3204.2, U3201.41
/CELL3/DAC2/TMP: TP3201.1, U3201.77
/CELL3/DAC3/AVDD_3P3V: C3313.1, U3301.75, U3301.76
/CELL3/DAC3/COMP_H: C3316.1, U3301.17
/CELL3/DAC3/COMP_L: C3317.1, U3301.23
/CELL3/DAC3/COMP_T: C3315.1, U3301.34
/CELL3/DAC3/FS_ADJ: R3301.1, U3301.79
/CELL3/DAC3/IOUTN: R3303.1, U3301.5, U3301.6
/CELL3/DAC3/IOUTP: R3302.1, U3301.3, U3301.4
/CELL3/DAC3/OUT: C3316.2, C3317.2, J3301.1, U3301.19, U3301.20, U3301.21
/CELL3/DAC3/REFIO: C3314.1, U3301.78
/CELL3/DAC3/SDN_IO: C3320.1, U3301.80, U3302.4, U3303.2
/CELL3/DAC3/SYNC_D: R3304.2, U3301.41
/CELL3/DAC3/TMP: TP3301.1, U3301.77
/CELL3/DAC4/AVDD_3P3V: C3413.1, U3401.75, U3401.76
/CELL3/DAC4/COMP_H: C3416.1, U3401.17
/CELL3/DAC4/COMP_L: C3417.1, U3401.23
/CELL3/DAC4/COMP_T: C3415.1, U3401.34
/CELL3/DAC4/FS_ADJ: R3401.1, U3401.79
/CELL3/DAC4/IOUTN: R3403.1, U3401.5, U3401.6
/CELL3/DAC4/IOUTP: R3402.1, U3401.3, U3401.4
/CELL3/DAC4/OUT: C3416.2, C3417.2, J3401.1, U3401.19, U3401.20, U3401.21
/CELL3/DAC4/REFIO: C3414.1, U3401.78
/CELL3/DAC4/SDN_IO: C3420.1, U3401.80, U3402.4, U3403.2
/CELL3/DAC4/SYNC_D: R3404.2, U3401.41
/CELL3/DAC4/TMP: TP3401.1, U3401.77
/CELL3/JTAGMODE: R3001.1, U3001.JB1.90
/CELL3/P3V3: C3016.1, C3017.1, C3118.1, C3119.1, C3218.1, C3219.1, C3318.1, C3319.1, C3418.1, C3419.1, R3105.1, R3106.1, R3108.1, R3205.1, R3206.1, R3208.1, R3305.1, R3306.1, R3308.1, R3405.1, R3406.1, R3408.1, U3001.JB1.10, U3001.JB1.12, U3001.JB2.2, U3001.JB2.4, U3001.JB2.6, U3001.JB2.8, U3001.JB2.9, U3001.JB2.10, U3001.JB2.11, U3102.5, U3103.5, U3202.5, U3203.5, U3302.5, U3303.5, U3402.5, U3403.5
/CELL3/P3V3_IN: C3008.1, C3015.1, U3001.JB1.14, U3001.JB1.16, U3002.7, U3002.8, U3002.9
/CELL3/P5V: C3004.1, C3005.1, C3006.1, C3007.1, C3013.1, C3014.1, C3111.1, C3211.1, C3311.1, C3411.1, PS3001.6, U3001.JB1.2, U3001.JB1.4, U3001.JB1.6, U3001.JB2.1, U3001.JB2.3, U3001.JB2.5, U3001.JB2.7, U3002.3, U3002.4, U3101.42, U3201.42, U3301.42, U3401.42
/CELL3/PGOOD: TP3001.1, U3001.JB1.29
/CELL3/RESET_N: R3106.2, R3206.2, R3306.2, R3406.2, U3001.JB3.10, U3101.36, U3201.36, U3301.36, U3401.36
/CELL3/SCLK: U3001.JB3.7, U3101.39, U3201.39, U3301.39, U3401.39
/CELL3/SDI: U3001.JB3.8, U3101.38, U3201.38, U3301.38, U3401.38
/CELL3/SDN_DRV: R3109.1, R3209.1, R3309.1, R3409.1, U3001.JB3.14, U3102.2, U3202.2, U3302.2, U3402.2
/CELL3/SDN_FLAG1: U3001.JB3.16, U3103.4
/CELL3/SDN_FLAG2: U3001.JB3.19, U3203.4
/CELL3/SDN_FLAG3: U3001.JB3.20, U3303.4
/CELL3/SDN_FLAG4: U3001.JB3.21, U3403.4
/CELL3/SDN_OE_N: R3108.2, R3208.2, R3308.2, R3408.2, U3001.JB3.15, U3102.1, U3202.1, U3302.1, U3402.1
/CELL3/SDN_RESET: R3107.1, R3207.1, R3307.1, R3407.1, U3001.JB3.13, U3101.1, U3201.1, U3301.1, U3401.1
/CELL3/SDO: U3001.JB3.9, U3101.37, U3201.37, U3301.37, U3401.37
/CELL3/UART_MIO14: J3002.1, U3001.JB1.91
/CELL3/UART_MIO15: J3002.2, U3001.JB1.86
/CELL3/VIN_5: L3001.1, PS3001.1
/CELL3/VREF_5V: C3012.1, C3112.1, C3212.1, C3312.1, C3412.1, U3004.6, U3101.44, U3201.44, U3301.44, U3401.44
/CELL3/VREF_EN: R3002.1, U3001.JB3.22, U3003.3
/CELL3/VREF_IN: C3010.1, R3003.2, U3003.6, U3004.2
/CELL3/VREF_JTAG: J3001.1, U3001.JB2.92
/CELL3/VREF_NR: C3011.1, U3004.5
/CELL3/VREF_QOD: R3003.1, U3003.5
/CELL3/X_TCK: J3001.3, U3001.JB2.100
/CELL3/X_TDI: J3001.5, U3001.JB2.96
/CELL3/X_TDO: J3001.4, U3001.JB2.98
/CELL3/X_TMS: J3001.2, U3001.JB2.94
/CELL4/BOOT_MODE: J4003.1, U4001.JB1.31
/CELL4/D1_CS_N: R4105.2, U4001.JB1.50, U4101.40
/CELL4/D1_DB0: U4001.JB1.32, U4101.53
/CELL4/D1_DB1: U4001.JB1.34, U4101.54
/CELL4/D1_DB2: U4001.JB1.35, U4101.55
/CELL4/D1_DB3: U4001.JB1.36, U4101.56
/CELL4/D1_DB4: U4001.JB1.37, U4101.57
/CELL4/D1_DB5: U4001.JB1.38, U4101.58
/CELL4/D1_DB6: U4001.JB1.39, U4101.59
/CELL4/D1_DB7: U4001.JB1.41, U4101.60
/CELL4/D1_DB8: U4001.JB1.42, U4101.61
/CELL4/D1_DB9: U4001.JB1.44, U4101.62
/CELL4/D1_DB10: U4001.JB1.45, U4101.63
/CELL4/D1_DB11: U4001.JB1.46, U4101.64
/CELL4/D1_DB12: U4001.JB1.47, U4101.65
/CELL4/D1_DB13: U4001.JB1.48, U4101.66
/CELL4/D1_SYNC: R4104.1, U4001.JB1.49
/CELL4/D2_CS_N: R4205.2, U4001.JB1.70, U4201.40
/CELL4/D2_DB0: U4001.JB1.51, U4201.53
/CELL4/D2_DB1: U4001.JB1.52, U4201.54
/CELL4/D2_DB2: U4001.JB1.55, U4201.55
/CELL4/D2_DB3: U4001.JB1.56, U4201.56
/CELL4/D2_DB4: U4001.JB1.57, U4201.57
/CELL4/D2_DB5: U4001.JB1.58, U4201.58
/CELL4/D2_DB6: U4001.JB1.59, U4201.59
/CELL4/D2_DB7: U4001.JB1.60, U4201.60
/CELL4/D2_DB8: U4001.JB1.61, U4201.61
/CELL4/D2_DB9: U4001.JB1.62, U4201.62
/CELL4/D2_DB10: U4001.JB1.65, U4201.63
/CELL4/D2_DB11: U4001.JB1.66, U4201.64
/CELL4/D2_DB12: U4001.JB1.67, U4201.65
/CELL4/D2_DB13: U4001.JB1.68, U4201.66
/CELL4/D2_SYNC: R4204.1, U4001.JB1.69
/CELL4/D3_CS_N: R4305.2, U4001.JB2.54, U4301.40
/CELL4/D3_DB0: U4001.JB2.31, U4301.53
/CELL4/D3_DB1: U4001.JB2.33, U4301.54
/CELL4/D3_DB2: U4001.JB2.35, U4301.55
/CELL4/D3_DB3: U4001.JB2.37, U4301.56
/CELL4/D3_DB4: U4001.JB2.41, U4301.57
/CELL4/D3_DB5: U4001.JB2.42, U4301.58
/CELL4/D3_DB6: U4001.JB2.43, U4301.59
/CELL4/D3_DB7: U4001.JB2.44, U4301.60
/CELL4/D3_DB8: U4001.JB2.45, U4301.61
/CELL4/D3_DB9: U4001.JB2.46, U4301.62
/CELL4/D3_DB10: U4001.JB2.47, U4301.63
/CELL4/D3_DB11: U4001.JB2.48, U4301.64
/CELL4/D3_DB12: U4001.JB2.51, U4301.65
/CELL4/D3_DB13: U4001.JB2.52, U4301.66
/CELL4/D3_SYNC: R4304.1, U4001.JB2.53
/CELL4/D4_CS_N: R4405.2, U4001.JB2.74, U4401.40
/CELL4/D4_DB0: U4001.JB2.55, U4401.53
/CELL4/D4_DB1: U4001.JB2.56, U4401.54
/CELL4/D4_DB2: U4001.JB2.57, U4401.55
/CELL4/D4_DB3: U4001.JB2.58, U4401.56
/CELL4/D4_DB4: U4001.JB2.61, U4401.57
/CELL4/D4_DB5: U4001.JB2.62, U4401.58
/CELL4/D4_DB6: U4001.JB2.63, U4401.59
/CELL4/D4_DB7: U4001.JB2.64, U4401.60
/CELL4/D4_DB8: U4001.JB2.65, U4401.61
/CELL4/D4_DB9: U4001.JB2.66, U4401.62
/CELL4/D4_DB10: U4001.JB2.67, U4401.63
/CELL4/D4_DB11: U4001.JB2.68, U4401.64
/CELL4/D4_DB12: U4001.JB2.71, U4401.65
/CELL4/D4_DB13: U4001.JB2.72, U4401.66
/CELL4/D4_SYNC: R4404.1, U4001.JB2.73
/CELL4/DAC1/AVDD_3P3V: C4113.1, U4101.75, U4101.76
/CELL4/DAC1/COMP_H: C4116.1, U4101.17
/CELL4/DAC1/COMP_L: C4117.1, U4101.23
/CELL4/DAC1/COMP_T: C4115.1, U4101.34
/CELL4/DAC1/FS_ADJ: R4101.1, U4101.79
/CELL4/DAC1/IOUTN: R4103.1, U4101.5, U4101.6
/CELL4/DAC1/IOUTP: R4102.1, U4101.3, U4101.4
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
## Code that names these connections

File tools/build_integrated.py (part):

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SHARED = ["SCLK", "SDI", "SDO", "RESET_N", "SDN_RESET", "SDN_DRV", "SDN_OE_N"]
FLAGS = [f"SDN_FLAG{j}" for j in range(1, N_DAC + 1)]
INTER = ["F_TRIG_IN", "F_TRIG_OUT", "F_SCLK", "F_MOSI", "F_MISO", "F_CS0", "F_CS1", "F_CS2", "F_EN", "F_CLK_SEL", "F_TRIG_SEL"]
MASTER_ONLY = {"F_EN", "F_CLK_SEL", "F_TRIG_SEL", "F_TRIG_OUT"}  # These pins are left unconnected at root on Slave cells
# PHY_COM is not connected: the Trenz TE0705 carrier also just leaves it on the connector
ETH = [f"PHY_MDI{i}_{s}" for i in range(4) for s in "PN"]
POWER_NETS = ["P24V_F", "GND_A", "P9V", "P52V", "N52V", "GND_B_300V"]
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    # DAC sheet ×4
    pos_list = [(431.8, 25.4), (508, 25.4), (431.8, 106.68), (508, 106.68)]
    for j in range(1, N_DAC + 1):
        pins = [(n, "input", "L") for n in DAC_SIGNALS + ["SCLK", "SDI"]] + [("SDO", "tri_state", "L")]
        pins += [(n, "input", "L") for n in ("RESET_N", "SDN_RESET", "SDN_DRV", "SDN_OE_N")] + [("SDN_FLAG", "output", "L")]
        pins += [(n, "passive", "R") for n in ("P52V", "N52V", "P5V", "VREF_5V", "P3V3", "GND_B_300V")]
        pg = [(f"{p}/{dac_su[j]}", str(3 + (k * (N_DAC + 1)) + j)) for k, (p, _) in enumerate(cell_paths)]
        x, y = pos_list[j - 1]
        pp = s.sheet(f"DAC{j}", "ad8460.kicad_sch", dac_su[j], x, y, 25.4, pins, pg)
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                r.label(f"TRIG_{k}", xy[0], xy[1], side)
            elif n in MASTER_ONLY:
                if k == 1:
                    r.label({"F_TRIG_OUT": "MASTER_TRIG_OUT"}.get(n, n), xy[0], xy[1], side)
                else:
                    r.items.append(f'\t(no_connect\n\t\t(at {xy[0]} {xy[1]})\n\t\t(uuid "{uid()}")\n\t)\n')
            elif n == "P3V3":
                if k == 1:
                    r.label("CELL1_P3V3", xy[0], xy[1], side)  # Supply for the clock and trigger circuits
                else:
                    r.items.append(f'\t(no_connect\n\t\t(at {xy[0]} {xy[1]})\n\t\t(uuid "{uid()}")\n\t)\n')
            elif n in ("F_CS0", "F_CS1", "F_CS2"):
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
